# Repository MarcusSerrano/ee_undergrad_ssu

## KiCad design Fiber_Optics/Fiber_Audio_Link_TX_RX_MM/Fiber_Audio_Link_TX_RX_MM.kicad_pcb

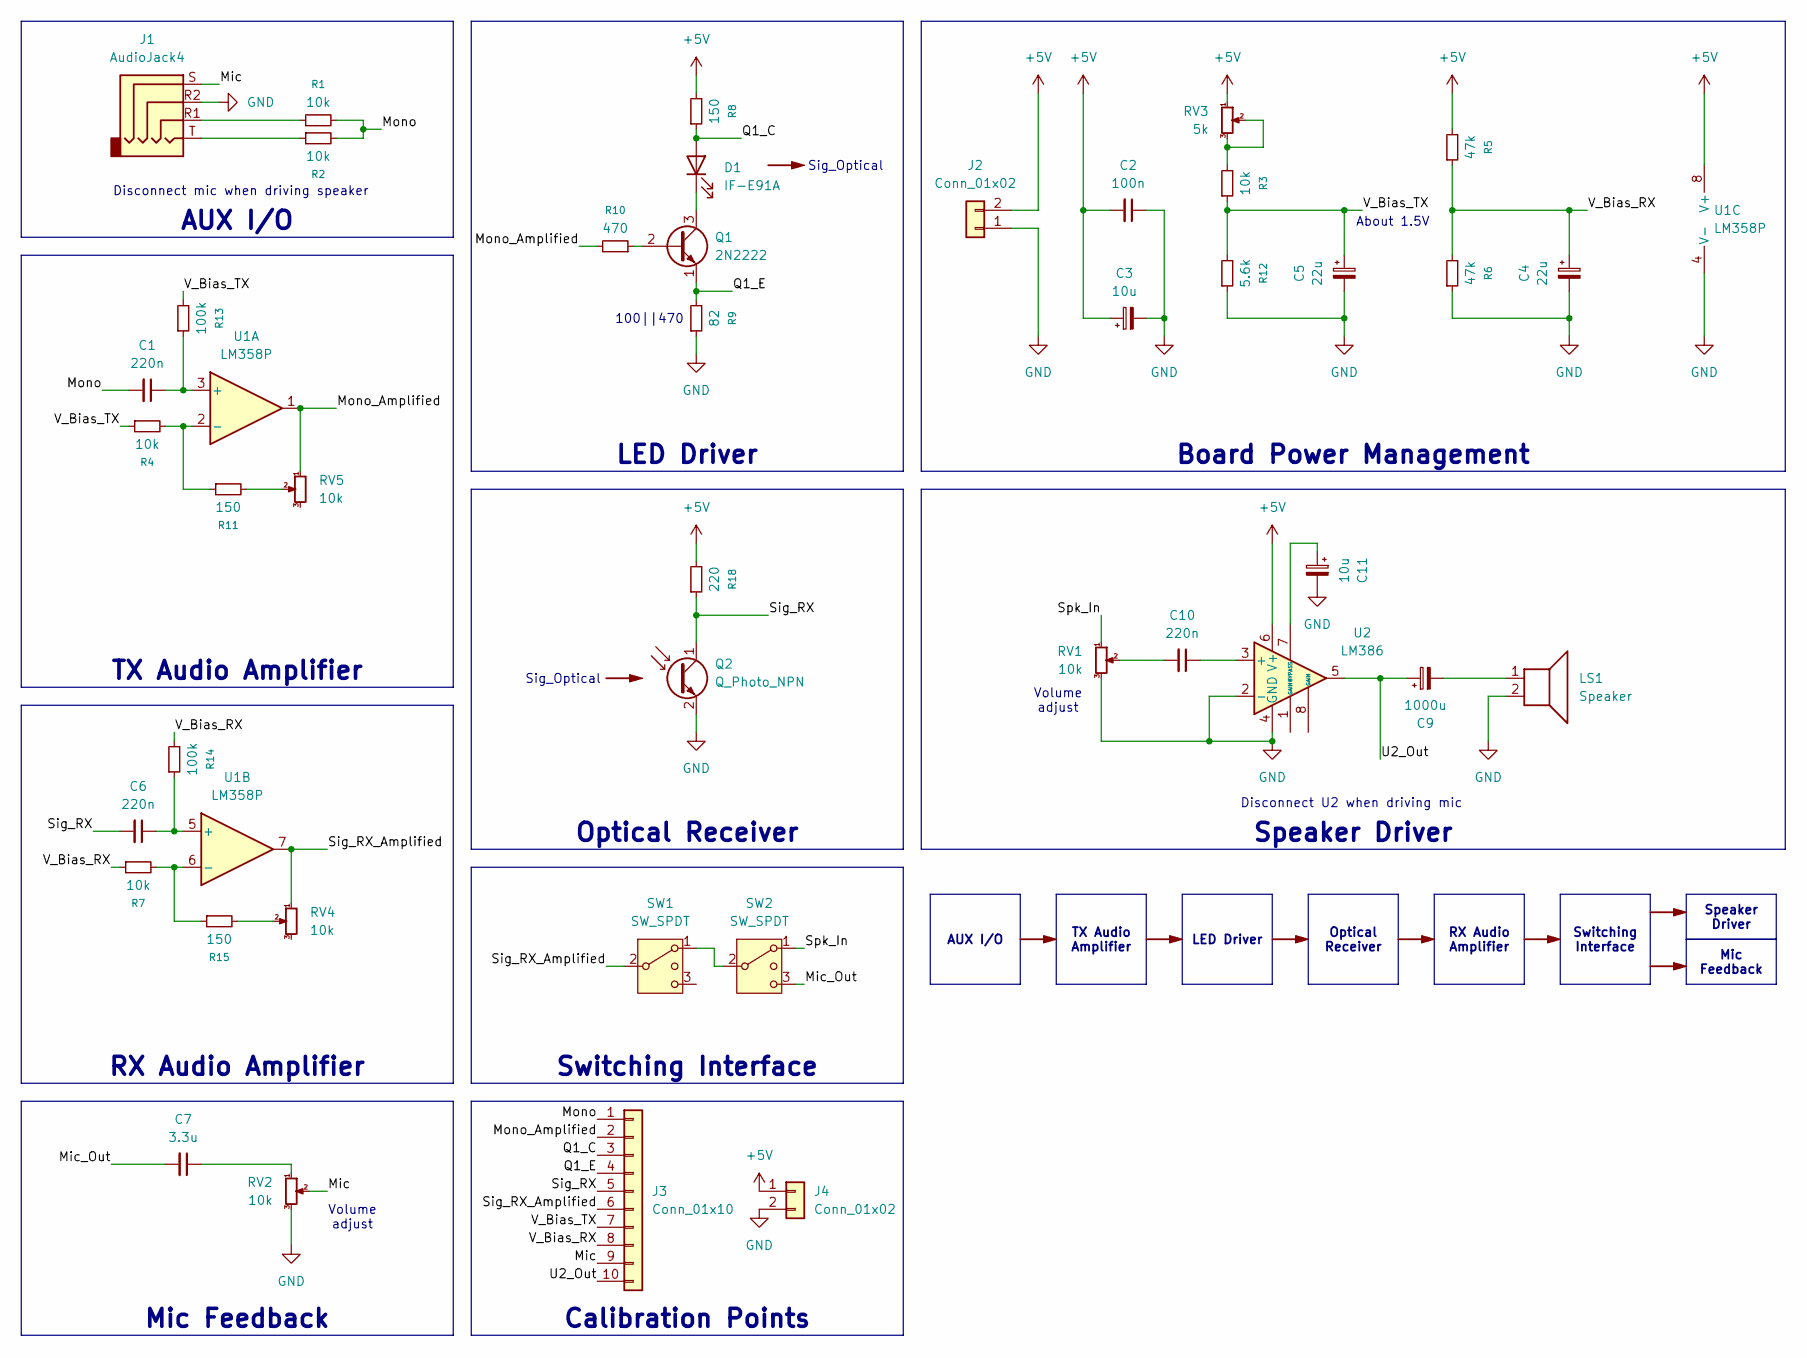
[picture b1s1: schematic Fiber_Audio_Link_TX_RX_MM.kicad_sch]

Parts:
C1, C6, C10: 220n; C_Disc_D3.0mm_W1.6mm_P2.50mm
C2: 100n; C_Disc_D3.0mm_W1.6mm_P2.50mm
C3, C11: 10u; CP_Radial_D5.0mm_P2.50mm
C4, C5: 22u; CP_Radial_D5.0mm_P2.50mm
C7: 3.3u; C_Disc_D3.0mm_W1.6mm_P2.50mm
C9: 1000u; CP_Radial_D10.0mm_P2.50mm
D1: IF-E91A; PinSocket_1x02_P2.54mm_Vertical
J1: AudioJack4; Jack_3.5mm_PJ320E_Horizontal
J2: Conn_01x02; PinHeader_1x02_P2.54mm_Vertical
J3: Conn_01x10; TerminalBlock_MaiXu_MX126-5.0-10P_1x10_P5.00mm
J4: Conn_01x02; TerminalBlock_MaiXu_MX126-5.0-02P_1x02_P5.00mm
LS1: Speaker; TerminalBlock_MaiXu_MX126-5.0-02P_1x02_P5.00mm
Q1: 2N2222; TO-92_Inline
Q2: Q_Photo_NPN; PinSocket_1x02_P2.54mm_Vertical
R1, R2, R3, R4, R7: 10k; R_Axial_DIN0207_L6.3mm_D2.5mm_P7.62mm_Horizontal
R5, R6: 47k; R_Axial_DIN0207_L6.3mm_D2.5mm_P7.62mm_Horizontal
R8, R11, R15: 150; R_Axial_DIN0207_L6.3mm_D2.5mm_P7.62mm_Horizontal
R9: 82; R_Axial_DIN0207_L6.3mm_D2.5mm_P7.62mm_Horizontal
R10: 470; R_Axial_DIN0207_L6.3mm_D2.5mm_P7.62mm_Horizontal
R12: 5.6k; R_Axial_DIN0207_L6.3mm_D2.5mm_P7.62mm_Horizontal
R13, R14: 100k; R_Axial_DIN0207_L6.3mm_D2.5mm_P7.62mm_Horizontal
R18: 220; R_Axial_DIN0207_L6.3mm_D2.5mm_P7.62mm_Horizontal
RV1, RV2, RV4, RV5: 10k; Potentiometer_Bourns_3266Y_Vertical
RV3: 5k; Potentiometer_Bourns_3266Y_Vertical
SW1, SW2: SW_SPDT; PinHeader_1x03_P2.54mm_Vertical
U1: LM358P; DIP-8_W7.62mm_LongPads
U2: LM386; DIP-8_W7.62mm_LongPads

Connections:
+5V: C2.2, C3.1, J2.2, J4.1, R5.2, R8.2, R18.2, RV3.1, U1.8 (V+), U2.6 (V+)
/Mic: J1.S, J3.9, RV2.2
/Mic_Out: C7.2, SW2.3 (4)
/Mono: C1.2, J3.1, R1.2, R2.2
/Mono_Amplified: J3.2, R10.2, RV5.1, U1.1
/Q1_C: D1.2 (A), J3.3, R8.1
/Q1_E: J3.4, Q1.1 (E), R9.2
/Sig_RX: C6.2, J3.5, Q2.1 (C), R18.1
/Sig_RX_Amplified: J3.6, RV4.1, SW1.2 (3), U1.7
/Spk_In: RV1.1, SW2.1
/U2_Out: C9.1, J3.10, U2.5
/V_Bias_RX: C4.1, J3.8, R5.1, R6.2, R7.1, R14.2
/V_Bias_TX: C5.1, J3.7, R3.1, R4.1, R12.2, R13.2
GND: C2.1, C3.2, C4.2, C5.2, C11.2, J1.R2, J2.1, J4.2, LS1.2, Q2.2 (E), R6.1, R9.1, R12.1, RV1.3, RV2.3, U1.4 (V-), U2.2 (-), U2.4 (GND)
unnamed: C7.1, RV2.1
unnamed: C9.2, LS1.1
unnamed: C10.2, RV1.2
unnamed: D1.1 (K), Q1.3 (C)
unnamed: J1.R1, R1.1
unnamed: J1.T, R2.1
unnamed: Q1.2 (B), R10.1
unnamed: R3.2, RV3.2, RV3.3
unnamed: R11.2, RV5.2
unnamed: R15.2, RV4.2
unnamed: SW1.1, SW2.2 (3)
unnamed: C1.1, R13.1, U1.3 (+)
unnamed: R4.2, R11.1, U1.2 (-)
unnamed: C6.1, R14.1, U1.5 (+)
unnamed: R7.2, R15.1, U1.6 (-)
unnamed: C10.1, U2.3 (+)
unnamed: C11.1, U2.7 (BYPASS)

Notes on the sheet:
Volume adjust
Sig_Optical
100||470
About 1.5V
Disconnect U2 when driving mic
Disconnect mic when driving speaker
Calibration Points
Switching Interface
Speaker Driver
RX Audio Amplifier
Optical Receiver
LED Driver
TX Audio Amplifier
Mic Feedback
AUX I/O
Board Power Management

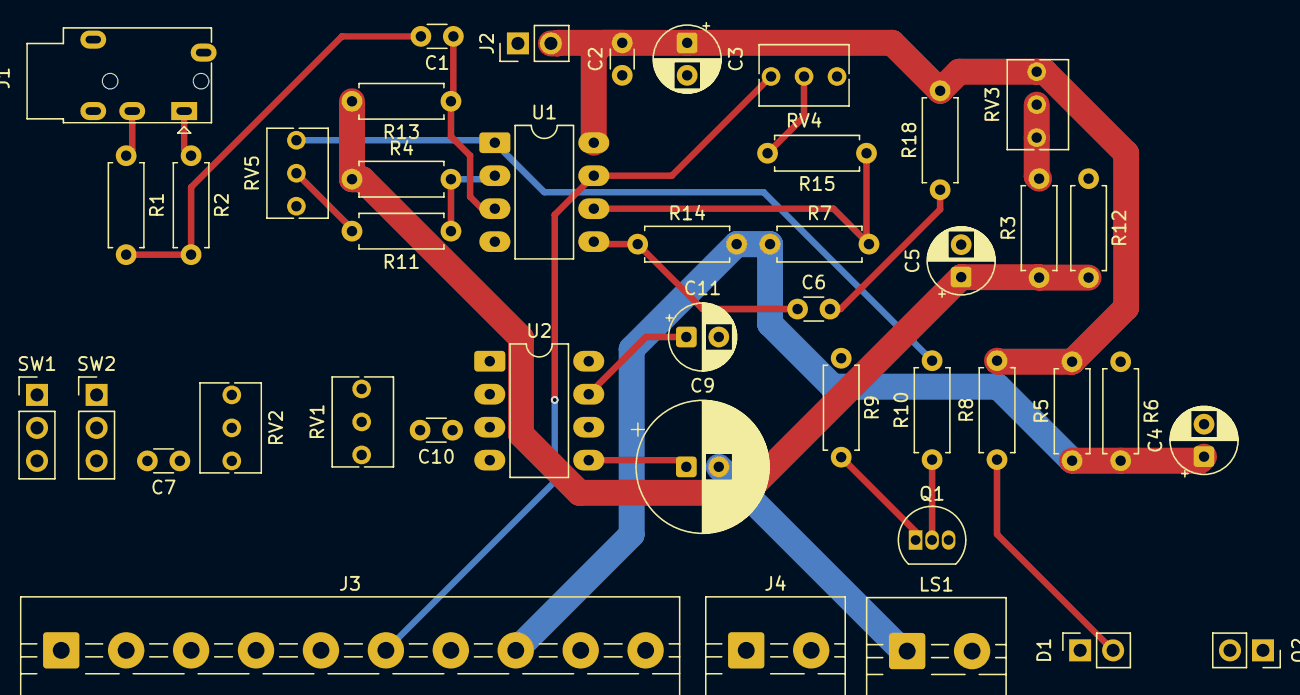
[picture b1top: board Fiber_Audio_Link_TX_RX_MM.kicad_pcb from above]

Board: 2 copper layers, 43 parts (0 on the bottom side), 31 nets.

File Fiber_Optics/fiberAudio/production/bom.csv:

Designator,Footprint,Quantity,Value,LCSC Part #
"C1, C10, C6",C_Disc_D3.0mm_W1.6mm_P2.50mm,3,220n,
"C11, C3",CP_Radial_D5.0mm_P2.50mm,2,10u,
C2,C_Disc_D3.0mm_W1.6mm_P2.50mm,1,100n,
"C4, C5",CP_Radial_D5.0mm_P2.50mm,2,22u,
C7,C_Disc_D3.0mm_W1.6mm_P2.50mm,1,3.3u,
C9,CP_Radial_D10.0mm_P2.50mm,1,1000u,
D1,PinSocket_1x02_P2.54mm_Vertical,1,IF-E91A,
J1,Jack_3.5mm_PJ320E_Horizontal,1,AudioJack4,
J2,PinHeader_1x06_P2.54mm_Vertical,1,Conn_01x06,
J3,TerminalBlock_MaiXu_MX126-5.0-10P_1x10_P5.00mm,1,Conn_01x10,
J4,TerminalBlock_MaiXu_MX126-5.0-02P_1x02_P5.00mm,1,Conn_01x02,
LS1,TerminalBlock_MaiXu_MX126-5.0-02P_1x02_P5.00mm,1,Speaker,
Q1,TO-92_Inline,1,2N2222,
Q2,PinSocket_1x02_P2.54mm_Vertical,1,Q_Photo_NPN,
"R1, R2, R3, R4, R7",R_Axial_DIN0207_L6.3mm_D2.5mm_P7.62mm_Horizontal,5,10k,
R10,R_Axial_DIN0207_L6.3mm_D2.5mm_P7.62mm_Horizontal,1,470,
"R11, R15, R8",R_Axial_DIN0207_L6.3mm_D2.5mm_P7.62mm_Horizontal,3,150,
R12,R_Axial_DIN0207_L6.3mm_D2.5mm_P7.62mm_Horizontal,1,5.6k,
"R13, R14",R_Axial_DIN0207_L6.3mm_D2.5mm_P7.62mm_Horizontal,2,100k,
R18,R_Axial_DIN0207_L6.3mm_D2.5mm_P7.62mm_Horizontal,1,220,
"R5, R6",R_Axial_DIN0207_L6.3mm_D2.5mm_P7.62mm_Horizontal,2,47k,
R9,R_Axial_DIN0207_L6.3mm_D2.5mm_P7.62mm_Horizontal,1,82,
"RV1, RV2, RV4, RV5",Potentiometer_Bourns_3266Y_Vertical,4,10k,
RV3,Potentiometer_Bourns_3266Y_Vertical,1,5k,
"SW1, SW2",PinHeader_1x03_P2.54mm_Vertical,2,SW_SPDT,
U1,DIP-8_W7.62mm_LongPads,1,LM358P,
U2,DIP-8_W7.62mm_LongPads,1,LM386,

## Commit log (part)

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2026-03-28 Add fiber assignments.
2026-05-15 update fiber audio link project.
